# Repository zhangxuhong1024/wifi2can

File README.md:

# CAN2WIFI使用说明

----------------
### 概述
* 我给这个板子取了个响当当的名字；***CAN2WIFI***。
* CAN2WIFI使用MicroPython作为主控，预留USB模拟串口作为MicroPython串口终端，可通过此接口来进行操作CAN2WIFI。
也就是说，你可以直接通过MicroPython干你想干的事情，包括直接修改软件。
以上，是针对大神说的。如果你不是，那抱歉了。
如果不会Python，那就可以跳过串口调试部分了，请使用上位机提供的有限功能。
* 沙发上
* 此板子包含的接口有：
        CAN2.0A/B *1 
        USB串口 *1
        国标充电CP模拟信号发生器 *1
        低控继电器开关 *1
        模拟电压检测 *1

:
:
:
:
:
:
:

----------------
### MicroPython串口调试：
* 使用串口调试，必须先引用can2wifi模块。
```
import can2wifi
```

----------------
### 上位机设置：
待补充

----------------
### LED显示说明：
LED1: **系统运行指示灯**
* 系统正常运行时，呼吸闪烁。

LED2: **数据指示灯**
* 闪烁： 收到报文并成功发送到上位机/SD卡
        亮-收到报文
        灭-报文写入到SD卡或发送到上位机

LED3: **错误指示灯**
* 报文溢出
* 报文发送失败
* SD卡错误
* WIFI连接错误
* 串口通信错误

----------------
芯片引脚连接定义：

序号 |ESP8266 |MCP2515 |SD卡  |IO接口 |备注
-----|--------|--------|------|-------|--
1    |GPIO5   |CS      |      |       |
2    |GPIO4   |INT     |      |       |
3    |GPIO16  |        |CS    |       |
4    |GPIO13  |MOSI    |DI    |       |HSPI_MOSI
5    |GPIO14  |CLK     |CLK   |       |HSPI_CLK 
7    |GPIO12  |MISO    |DO    |       |HSPI_MISO
8    |ADC     |        |      |Ai     |
9    |GPIO0   |        |      |CP     |默认高电平，上电低电平则进入下载模式
10   |GPIO15  |        |      |RELAY  |默认低电平
11   |GPIO2   |        |      |LED1   |默认高电平
12   |        |RX0BF   |      |LED2   |
13   |        |RX1BF   |      |LED3   |

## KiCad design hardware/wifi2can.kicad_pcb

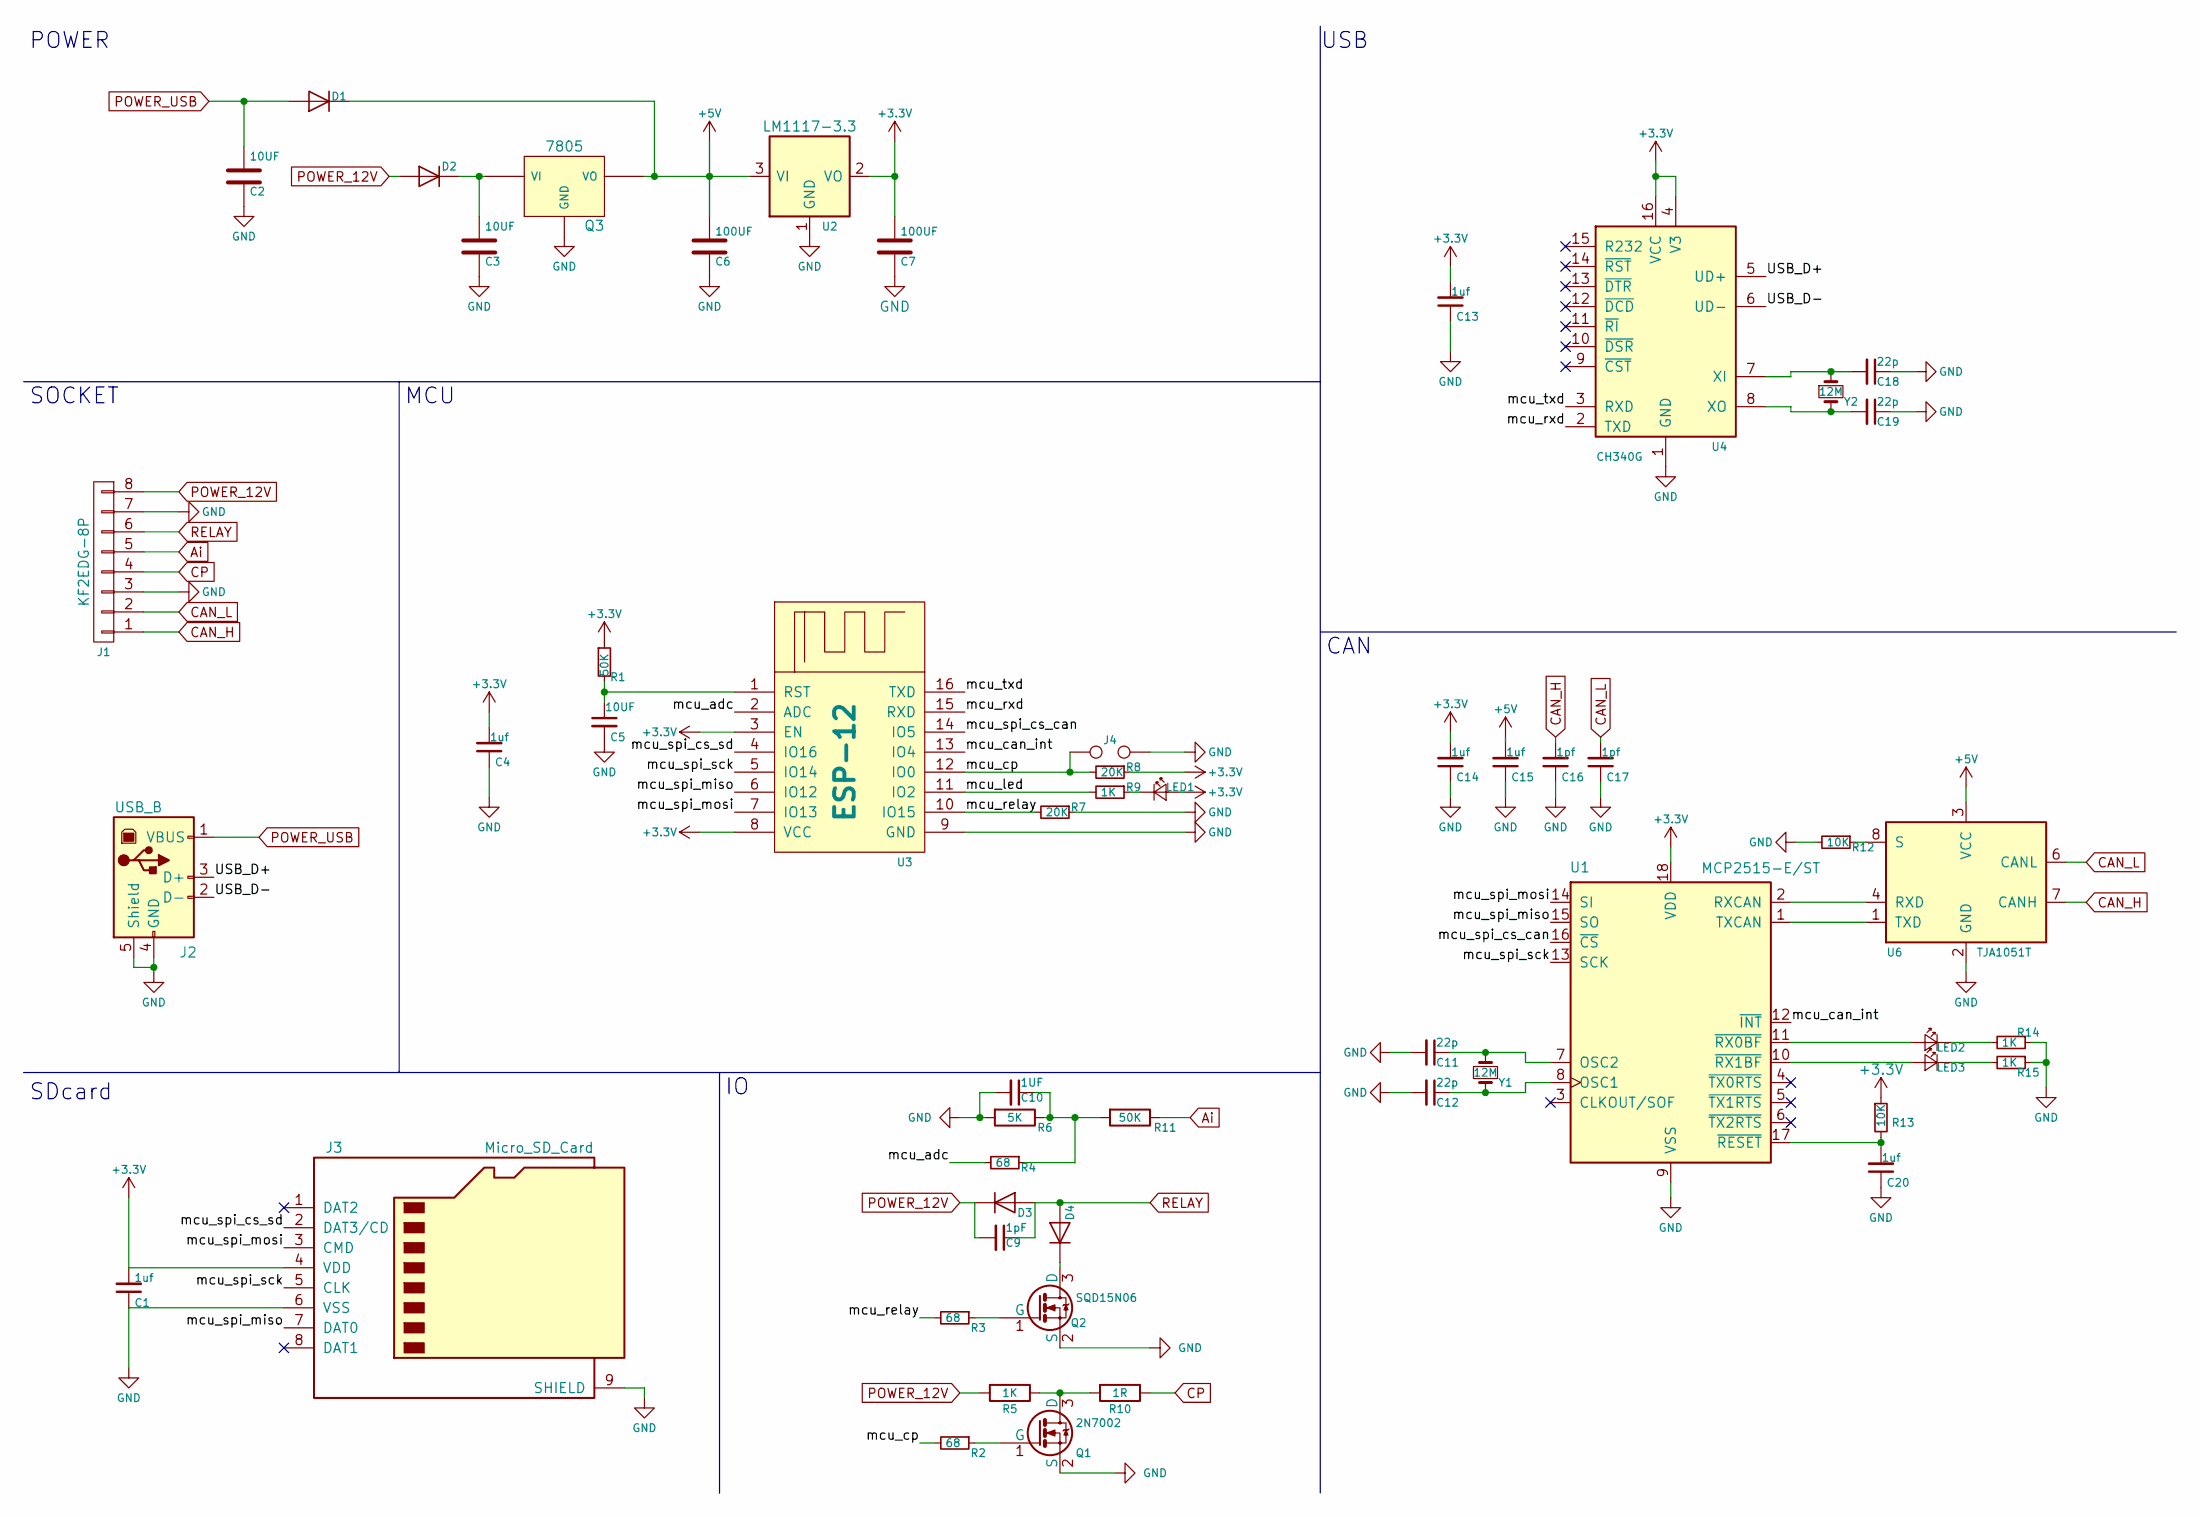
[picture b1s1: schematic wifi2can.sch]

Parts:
C1, C4, C13, C14, C15, C20: 1uf; C_0805
C2, C3, C5: 10UF; C_0805
C6, C7: 100UF; CP_Elec_8x6.7
C9: 1pF; C_0805
C10: 1UF; C_0805
C11, C12, C18, C19: 22p; C_0805
C16, C17: 1pf; C_0805
D1, D2, D3, D4: D; D_SMB_Handsoldering
J1: KF2EDG-8P; PhoenixContact_MC-G_08x3.81mm_Angled
J2: USB_B
J3: Micro_SD_Card; TF(Micro-SD)
J4: download; wifi2can_download
LED1, LED2, LED3: LED_Small; LED_1206
Q1: 2N7002; SOT-23
Q2: SQD15N06; TO-252-2Lead
Q3: 7805; 78m05
R1, R11: 50K; R_0805
R2, R3, R4: 68; R_0805
R5, R9, R14, R15: 1K; R_0805
R6: 5K; R_0805
R7, R8: 20K; R_0805
R10: 1R; R_0805
R12, R13: 10K; R_0805
U1: MCP2515-E/ST; SOIC-18W_7.5x11.6mm_Pitch1.27mm
U2: LM1117-3.3; SOT-223-3Lead_TabPin2
U3: ESP-12; ESP-12E_SMD
U4: CH340G; SOIC-16_3.9x9.9mm_Pitch1.27mm
U6: TJA1051T; SOIC-8_3.9x4.9mm_Pitch1.27mm
Y1, Y2: 12M; Crystal_SMD_5032-4pin_5.0x3.2mm

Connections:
+3V3: C1.2, C4.2, C7.1, C13.2, C14.2, J3.4 (VDD), LED1.2 (A), R1.1, R8.1, R13.1, U1.18 (VDD), U2.2 (VO), U3.3 (EN), U3.8 (VCC), U4.4 (V3), U4.16 (VCC)
+5V: C6.1, C15.2, D1.1 (K), Q3.VO, U2.3 (VI), U6.3 (VCC)
/USB_D+: J2.3 (D+), U4.5 (UD+)
/USB_D-: J2.2 (D-), U4.6 (UD-)
/mcu_adc: R4.2, U3.2 (ADC)
/mcu_can_int: U1.12 (~INT), U3.13 (IO4)
/mcu_cp: J4.1, R2.2, R8.2, U3.12 (IO0)
/mcu_led: R9.2, U3.11 (IO2)
/mcu_relay: R3.2, R7.2, U3.10 (IO15)
/mcu_rxd: U3.15 (RXD), U4.2 (TXD)
/mcu_spi_cs_can: U1.16 (~CS), U3.14 (IO5)
/mcu_spi_cs_sd: J3.2 (DAT3/CD), U3.4 (IO16)
/mcu_spi_miso: J3.7 (DAT0), U1.15 (SO), U3.6 (IO12)
/mcu_spi_mosi: J3.3 (CMD), U1.14 (SI), U3.7 (IO13)
/mcu_spi_sck: J3.5 (CLK), U1.13 (SCK), U3.5 (IO14)
/mcu_txd: U3.16 (TXD), U4.3 (RXD)
Ai: J1.5, R11.1
CAN_H: C16.2, J1.1, U6.7 (CANH)
CAN_L: C17.2, J1.2, U6.6 (CANL)
CP: J1.4, R10.1
GND: C1.1, C2.2, C3.2, C4.1, C5.2, C6.2, C7.2, C10.2, C11.2, C12.2, C13.1, C14.1, C15.1, C16.1, C17.1, C18.1, C19.1, C20.1, J1.3, J1.7, J2.4 (GND), J2.5 (Shield), J3.6 (VSS), J3.9 (SHIELD), J3.10, J4.2, Q1.2 (S), Q2.2 (S), Q3.GND, R6.2, R7.1, R12.2, R14.1, R15.1, U1.9 (VSS), U2.1 (GND), U3.9 (GND), U4.1 (GND), U6.2 (GND)
unnamed: C3.1, D2.1 (K), Q3.VI
unnamed: C5.1, R1.2, U3.1 (RST)
unnamed: C10.1, R4.1, R6.1, R11.2
unnamed: C11.1, U1.7 (OSC2), Y1.1
unnamed: C12.1, U1.8 (OSC1), Y1.2
unnamed: C18.2, U4.7 (XI), Y2.1
unnamed: C19.2, U4.8 (XO), Y2.2
unnamed: C20.2, R13.2, U1.17 (~RESET)
unnamed: D4.1 (K), Q2.3 (D)
unnamed: LED1.1 (K), R9.1
unnamed: LED2.1 (K), R14.2
unnamed: LED2.2 (A), U1.11 (~RX0BF)
unnamed: LED3.1 (K), R15.2
unnamed: LED3.2 (A), U1.10 (~RX1BF)
unnamed: Q1.1 (G), R2.1
unnamed: Q1.3 (D), R5.1, R10.2
unnamed: Q2.1 (G), R3.1
unnamed: R12.1, U6.8 (S)
unnamed: U1.1 (TXCAN), U6.1 (TXD)
unnamed: U1.2 (RXCAN), U6.4 (RXD)
POWER_12V: C9.2, D2.2 (A), D3.1 (K), J1.8, R5.2
POWER_USB: C2.1, D1.2 (A), J2.1 (VBUS)
RELAY: C9.1, D3.2 (A), D4.2 (A), J1.6

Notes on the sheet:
USB
POWER
SOCKET
MCU
CAN
SDcard

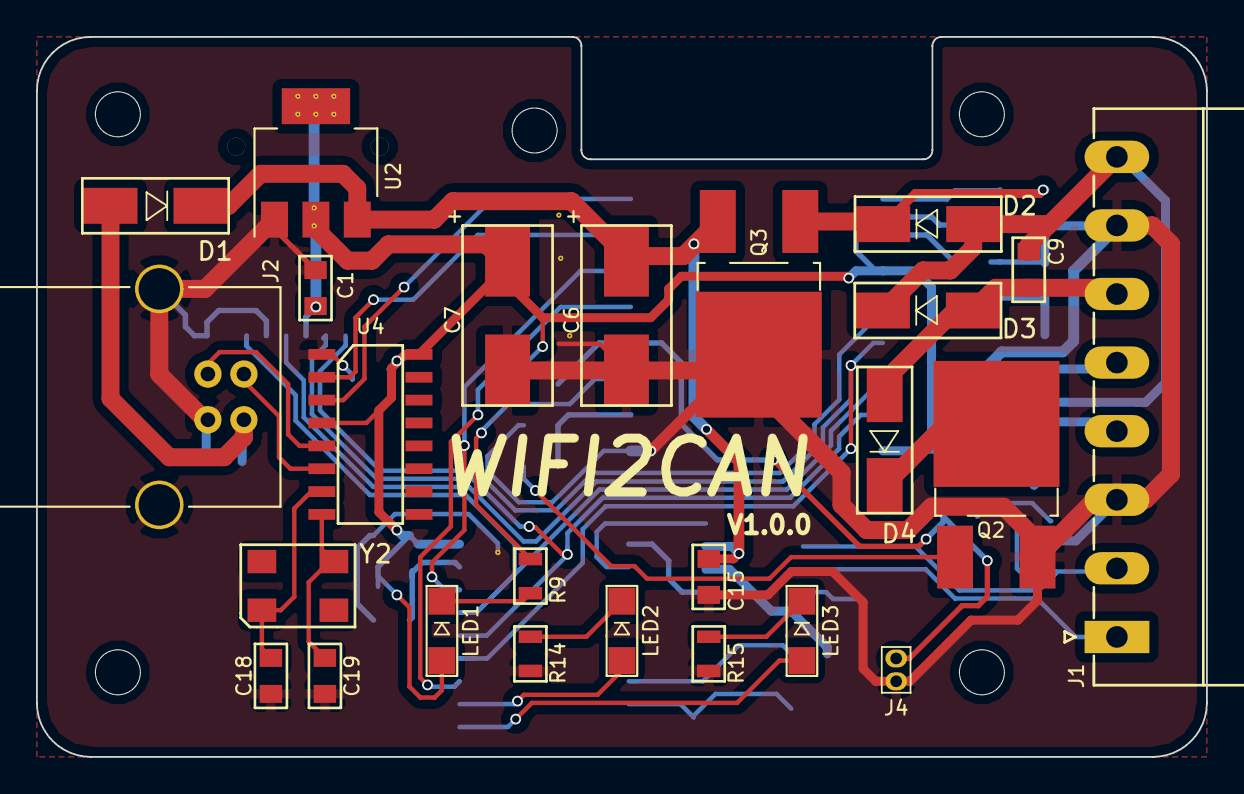
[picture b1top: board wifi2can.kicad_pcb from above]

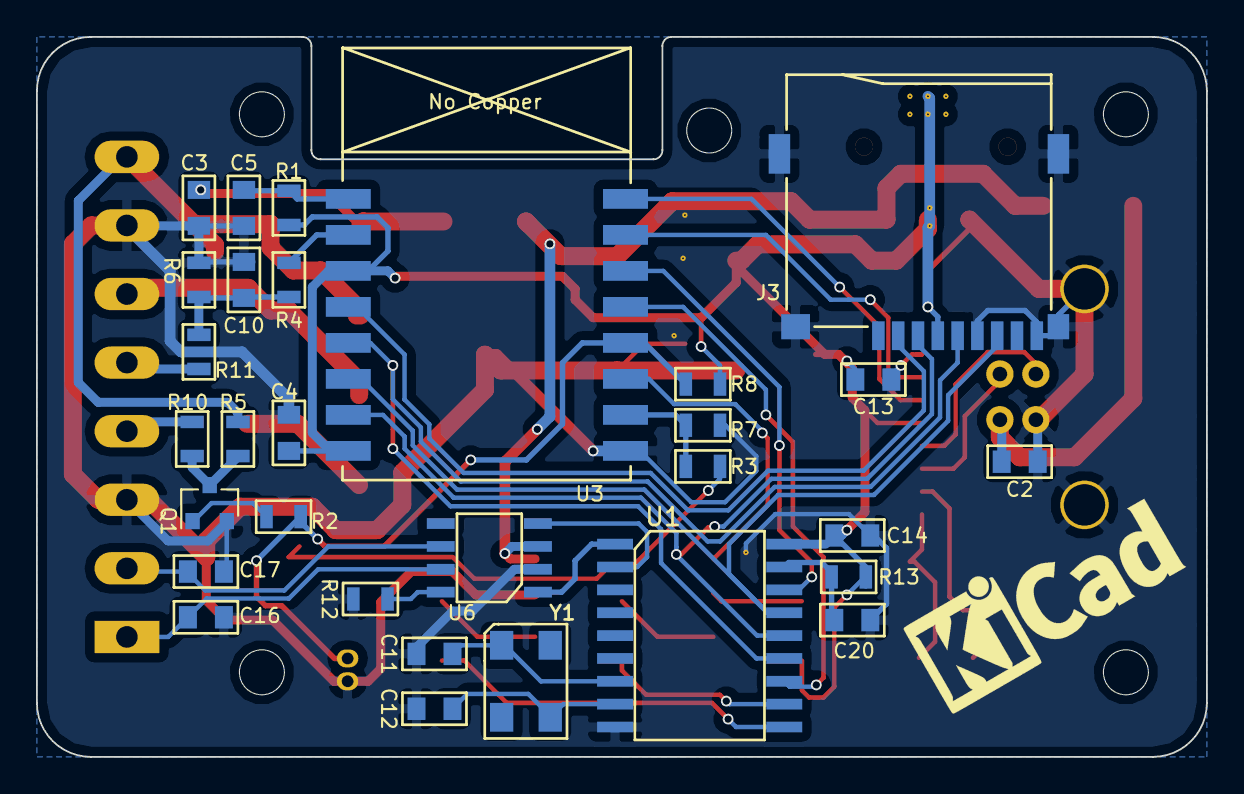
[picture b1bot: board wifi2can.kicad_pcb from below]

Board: 2 copper layers, 65.0 x 40.0 mm, 55 parts (30 on the bottom side), 44 nets.

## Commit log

2018-11-23 Add documents.
    Add 增加文档资料
2018-11-23 Add hardware.
    Add 增加硬件设计资料。
    Doc Kicad_V4.0.7
2018-11-23 Add program
    Add MicroPython软件
2019-02-20 临时拷贝个文件
